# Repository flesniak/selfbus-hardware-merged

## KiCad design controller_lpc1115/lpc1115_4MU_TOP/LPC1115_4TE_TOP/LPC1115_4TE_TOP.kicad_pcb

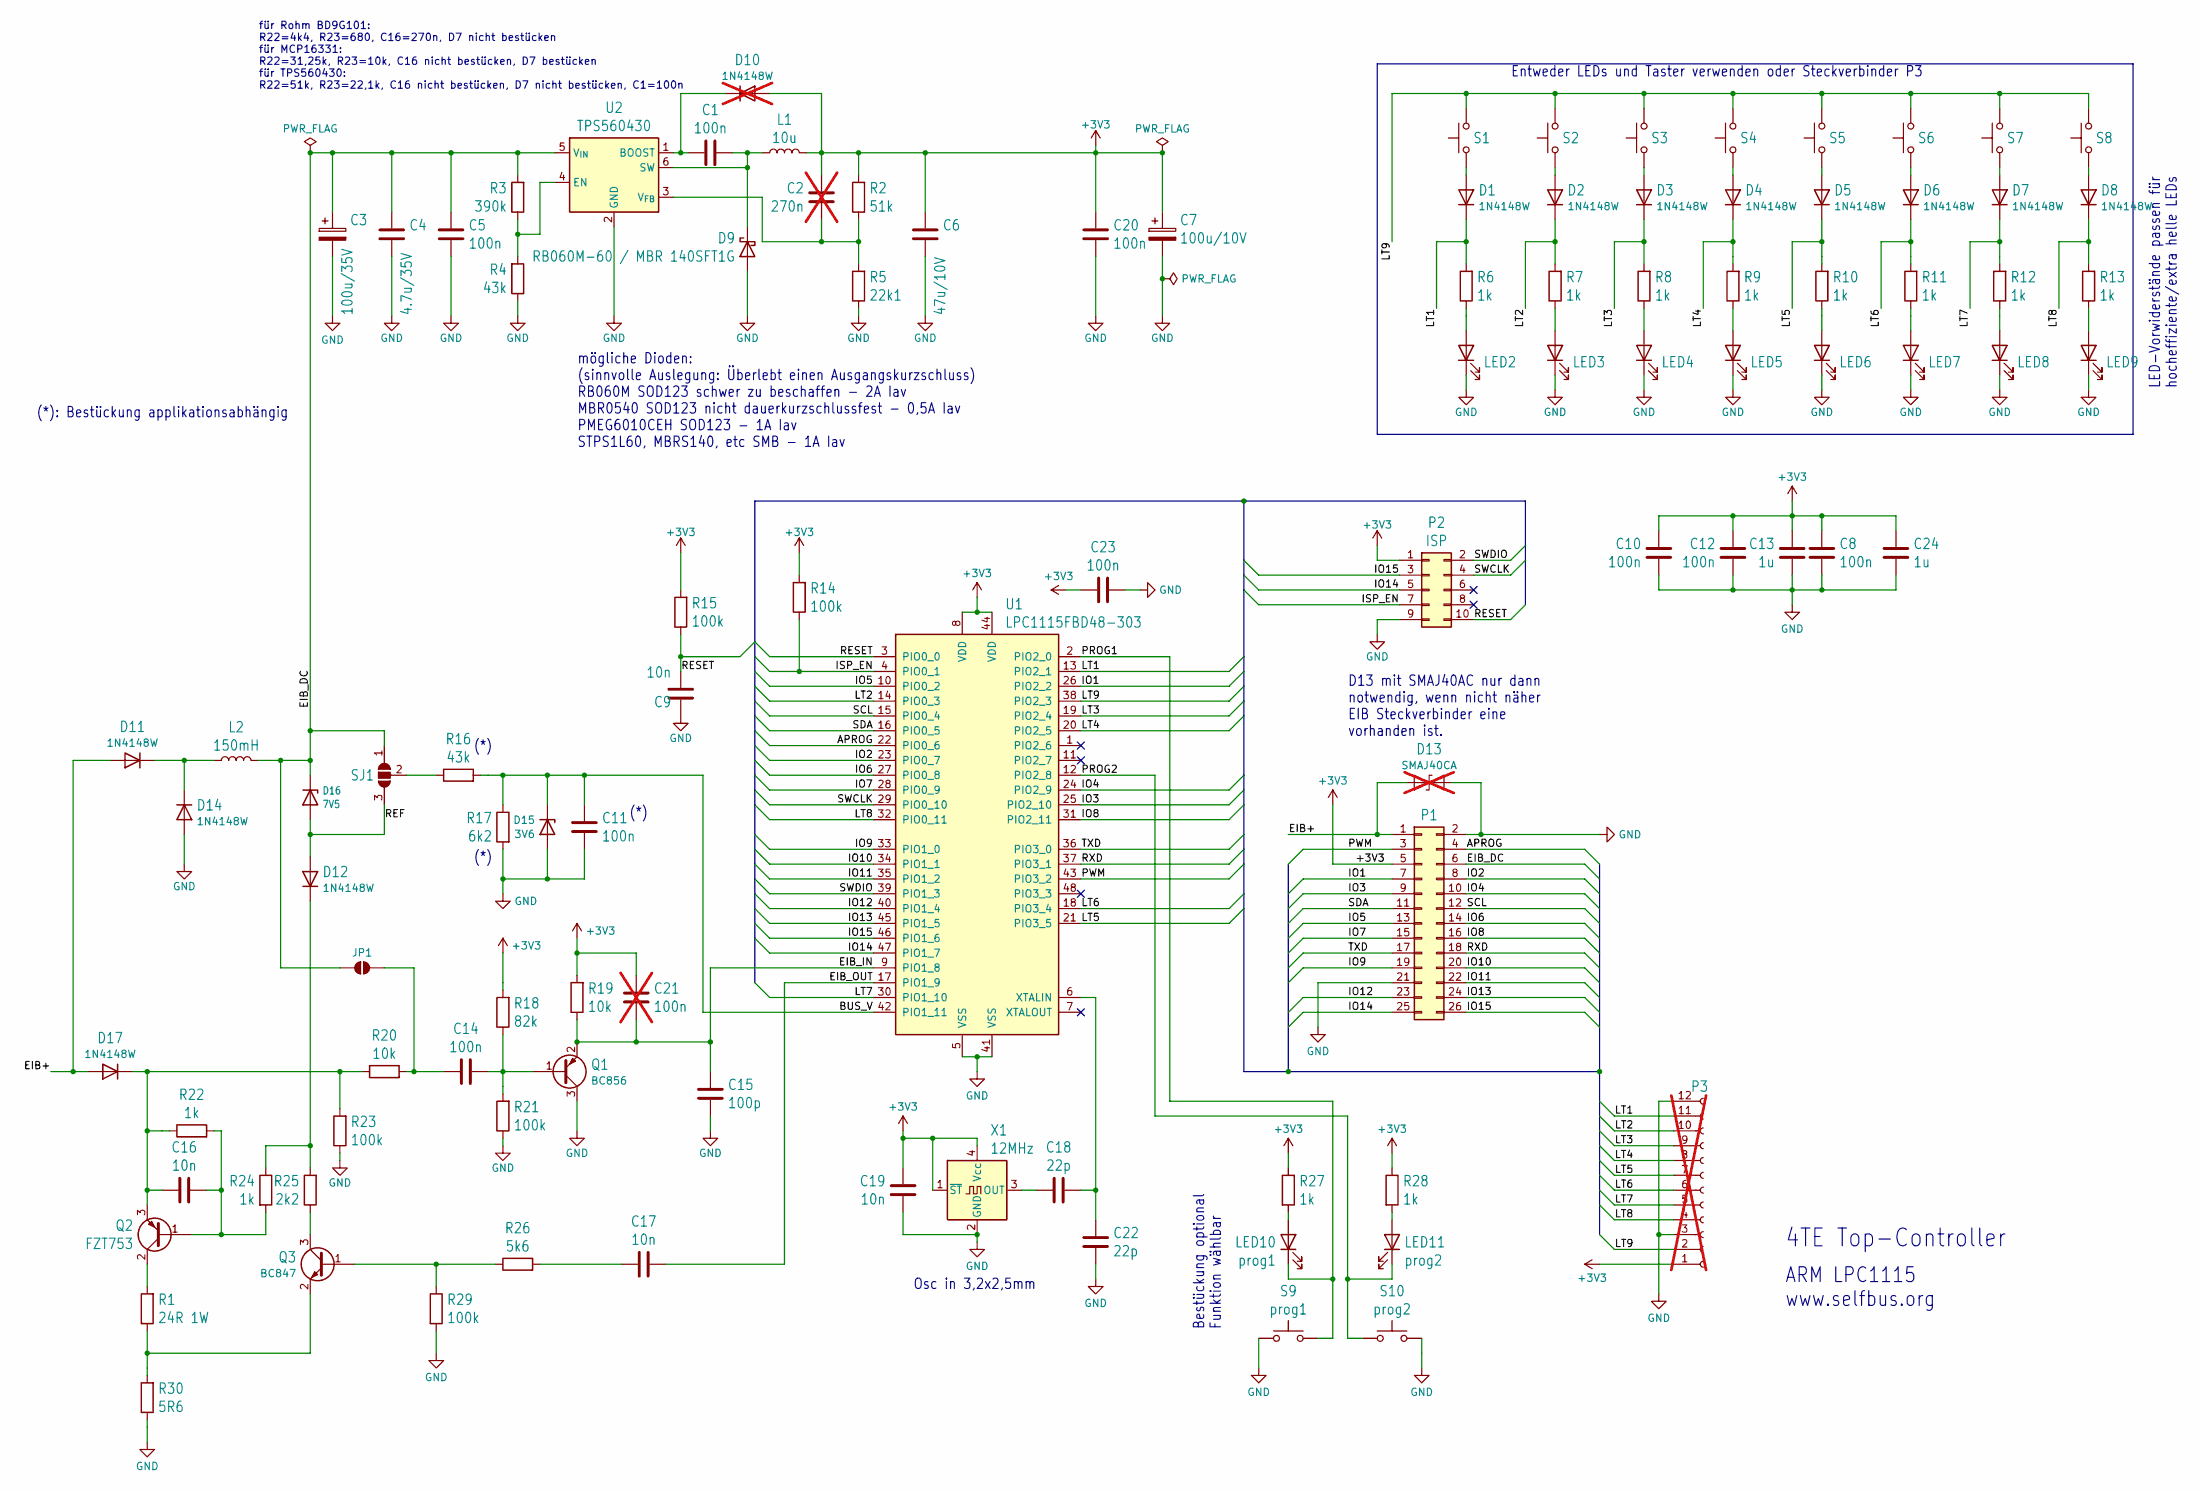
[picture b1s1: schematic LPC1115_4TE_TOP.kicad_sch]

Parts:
C1, C5, C8, C10, C11, C12, C14, C20, C23: 100n; C_0805_2012Metric
C2: 270n; C_0805_2012Metric; not fitted
C3: 100u/35V; CP_Elec_6.3x7.7
C4: 4.7u/35V; C_0805_2012Metric
C6: 47u/10V; C_1206_3216Metric
C7: 100u/10V; CP_Elec_6.3x7.7
C9, C16, C17, C19: 10n; C_0805_2012Metric
C13, C24: 1u; C_0805_2012Metric
C15: 100p; C_0805_2012Metric
C18, C22: 22p; C_0805_2012Metric
C21: 100n; C_0805_2012Metric; not fitted
D1, D2, D3, D4, D5, D6, D7, D8, D11, D12, D14, D17: 1N4148W; D_SOD-123
D9: RB060M-60 / MBR 140SFT1G; D_SOD-123
D10: 1N4148W; D_SOD-123; not fitted
D13: SMAJ40CA; D_SMA; not fitted
D15: 3V6; D_MiniMELF
D16: 7V5; D_MiniMELF
JP1: SolderJumper_2_Open; SolderJumper-2_P1.3mm_Open_Pad1.0x1.5mm
L1: 10u; L_1812_4532Metric
L2: 150mH; BS11_LIEGEND
LED2: CH1; LED_0805_2012Metric
LED3: CH2; LED_0805_2012Metric
LED4: CH3; LED_0805_2012Metric
LED5: CH4; LED_0805_2012Metric
LED6: CH5; LED_0805_2012Metric
LED7: CH6; LED_0805_2012Metric
LED8: CH7; LED_0805_2012Metric
LED9: CH8; LED_0805_2012Metric
LED10: prog1; LED_0805_2012Metric
LED11: prog2; LED_0805_2012Metric
P1: ML26; IDC-Header_2x13_P2.54mm_Vertical
P2: ISP; PinHeader_2x05_P2.00mm_Vertical
P3: FE12-1; PinHeader_1x12_P2.54mm_Vertical; not fitted
Q1: BC856; SOT-23
Q2: FZT753; SOT-223-3_TabPin2
Q3: BC847; SOT-23
R1: 24R 1W; R_2512_6332Metric
R2: 51k; R_0805_2012Metric
R3: 390k; R_0805_2012Metric
R4, R16: 43k; R_0805_2012Metric
R5: 22k1; R_0805_2012Metric
R6, R7, R8, R9, R10, R11, R12, R13, R22, R24, R27, R28: 1k; R_0805_2012Metric
R14, R15, R21, R23, R29: 100k; R_0805_2012Metric
R17: 6k2; R_0805_2012Metric
R18: 82k; R_0805_2012Metric
R19, R20: 10k; R_0805_2012Metric
R25: 2k2; R_0805_2012Metric
R26: 5k6; R_0805_2012Metric
R30: 5R6; R_0805_2012Metric
S1: CH1; SW_SPST_Omron_B3FS-100xP
S2: CH2; SW_SPST_Omron_B3FS-100xP
S3: CH3; SW_SPST_Omron_B3FS-100xP
S4: CH4; SW_SPST_Omron_B3FS-100xP
S5: CH5; SW_SPST_Omron_B3FS-100xP
S6: CH6; SW_SPST_Omron_B3FS-100xP
S7: CH7; SW_SPST_Omron_B3FS-100xP
S8: CH8; SW_SPST_Omron_B3FS-100xP
S9: prog1; SW_SPST_Omron_B3FS-100xP
S10: prog2; SW_SPST_Omron_B3FS-100xP
SJ1: SolderJumper_3_Open; SolderJumper-3_P1.3mm_Open_Pad1.0x1.5mm
U1: LPC1115FBD48-303; LQFP-48_7x7mm_P0.5mm
U2: TPS560430; SOT-23-6
X1: 12MHz; Oscillator_SMD_SeikoEpson_SG210-4Pin_2.5x2.0mm

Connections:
+3V3: C2.1, C6.1, C7.1, C8.1, C10.1, C12.1, C13.1, C19.1, C20.1, C21.2, C23.1, C24.1, D10.2 (A), L1.2, P1.5, P2.1, P3.1, R2.2, R14.2, R15.2, R18.2, R19.2, R27.1, R28.1, U1.8 (VDD), U1.44 (VDD), X1.1 (~ST), X1.4 (Vcc)
/APROG: P1.4, U1.22 (PIO0_6)
/BUS_V: C11.1, D15.1 (K), R16.2, R17.1, U1.42 (PIO1_11)
/EIB+: D11.2 (A), D13.2 (A2), D17.2 (A), P1.1
/EIB_DC: C3.1, C4.1, C5.1, D16.1 (K), JP1.1 (A), L2.2, P1.6, R3.2, SJ1.1 (A), U2.5 (V_{IN})
/EIB_IN: C15.2, C21.1, Q1.2 (E), R19.1, U1.9 (PIO1_8)
/EIB_OUT: C17.2, U1.17 (PIO1_9)
/IO1: P1.7, U1.26 (PIO2_2)
/IO2: P1.8, U1.23 (PIO0_7)
/IO3: P1.9, U1.25 (PIO2_10)
/IO4: P1.10, U1.24 (PIO2_9)
/IO5: P1.13, U1.10 (PIO0_2)
/IO6: P1.14, U1.27 (PIO0_8)
/IO7: P1.15, U1.28 (PIO0_9)
/IO8: P1.16, U1.31 (PIO2_11)
/IO9: P1.19, U1.33 (PIO1_0)
/IO10: P1.20, U1.34 (PIO1_1)
/IO11: P1.22, U1.35 (PIO1_2)
/IO12: P1.23, U1.40 (PIO1_4)
/IO13: P1.24, U1.45 (PIO1_5)
/IO14: P1.25, P2.5, U1.47 (PIO1_7)
/IO15: P1.26, P2.3, U1.46 (PIO1_6)
/ISP_EN: P2.7, R14.1, U1.4 (PIO0_1)
/LT1: D1.1 (K), P3.11, R6.2, U1.13 (PIO2_1)
/LT2: D2.1 (K), P3.10, R7.2, U1.14 (PIO0_3)
/LT3: D3.1 (K), P3.9, R8.2, U1.19 (PIO2_4)
/LT4: D4.1 (K), P3.8, R9.2, U1.20 (PIO2_5)
/LT5: D5.1 (K), P3.7, R10.2, U1.21 (PIO3_5)
/LT6: D6.1 (K), P3.6, R11.2, U1.18 (PIO3_4)
/LT7: D7.1 (K), P3.5, R12.2, U1.30 (PIO1_10)
/LT8: D8.1 (K), P3.4, R13.2, U1.32 (PIO0_11)
/LT9: P3.2, S1.1, S2.1, S3.1, S4.1, S5.1, S6.1, S7.1, S8.1, U1.38 (PIO2_3)
/PROG1: LED10.1 (K), S9.1, U1.2 (PIO2_0)
/PROG2: LED11.1 (K), S10.1, U1.12 (PIO2_8)
/PWM: P1.3, U1.43 (PIO3_2)
/REF: D12.2 (A), D16.2 (A), SJ1.3 (B)
/RESET: C9.2, P2.10, R15.1, U1.3 (PIO0_0)
/RXD: P1.18, U1.37 (PIO3_1)
/SCL: P1.12, U1.15 (PIO0_4)
/SDA: P1.11, U1.16 (PIO0_5)
/SWCLK: P2.4, U1.29 (PIO0_10)
/SWDIO: P2.2, U1.39 (PIO1_3)
/TXD: P1.17, U1.36 (PIO3_0)
GND: C3.2, C4.2, C5.2, C6.2, C7.2, C8.2, C9.1, C10.2, C11.2, C12.2, C13.2, C15.1, C19.2, C20.2, C22.2, C23.2, C24.2, D9.2 (A), D13.1 (A1), D14.2 (A), D15.2 (A), LED2.1 (K), LED3.1 (K), LED4.1 (K), LED5.1 (K), LED6.1 (K), LED7.1 (K), LED8.1 (K), LED9.1 (K), P1.2, P1.21, P2.9, P3.3, P3.12, Q1.3 (C), R4.1, R5.1, R17.2, R21.1, R23.1, R29.2, R30.1, S9.2, S10.2, U1.5 (VSS), U1.41 (VSS), U2.2 (GND), X1.2 (GND)
unnamed: C17.1, R26.2
unnamed: D1.2 (A), S1.2
unnamed: D2.2 (A), S2.2
unnamed: D3.2 (A), S3.2
unnamed: D4.2 (A), S4.2
unnamed: D5.2 (A), S5.2
unnamed: D6.2 (A), S6.2
unnamed: D7.2 (A), S7.2
unnamed: D8.2 (A), S8.2
unnamed: C1.1, D9.1 (K), L1.1, U2.6 (SW)
unnamed: C1.2, D10.1 (K), U2.1 (BOOST)
unnamed: D11.1 (K), D14.1 (K), L2.1
unnamed: D12.1 (K), R24.1, R25.2
unnamed: C16.1, D17.1 (K), Q2.3 (E), R20.1, R22.1, R23.2
unnamed: C14.1, JP1.2 (B), R20.2
unnamed: LED2.2 (A), R6.1
unnamed: LED3.2 (A), R7.1
unnamed: LED4.2 (A), R8.1
unnamed: LED5.2 (A), R9.1
unnamed: LED6.2 (A), R10.1
unnamed: LED7.2 (A), R11.1
unnamed: LED8.2 (A), R12.1
unnamed: LED9.2 (A), R13.1
unnamed: LED10.2 (A), R27.2
unnamed: LED11.2 (A), R28.2
unnamed: C14.2, Q1.1 (B), R18.1, R21.2
unnamed: C16.2, Q2.1 (B), R22.2, R24.2
unnamed: Q2.2 (C), R1.2
unnamed: Q3.1 (B), R26.1, R29.1
unnamed: Q3.3 (C), R25.1
unnamed: Q3.2 (E), R1.1, R30.2
unnamed: R16.1, SJ1.2 (C)
unnamed: C18.2, C22.1, U1.6 (XTALIN)
unnamed: R3.1, R4.2, U2.4 (EN)
unnamed: C2.2, R2.1, R5.2, U2.3 (V_{FB})
unnamed: C18.1, X1.3 (OUT)

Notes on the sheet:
4TE Top-Controller
(*): Bestückung applikationsabhängig
(*)
LED-Vorwiderstände passen für hocheffiziente/extra helle LEDs
mögliche Dioden: (sinnvolle Auslegung: Überlebt einen Ausgangskurzschluss) RB060M SOD123 schwer zu beschaffen - 2A Iav MBR0540 SOD123 nicht dauerkurzschlussfest - 0,5A Iav PMEG6010CEH SOD123 - 1A Iav STPS1L60, MBRS140, etc SMB - 1A Iav
Entweder LEDs und Taster verwenden oder Steckverbinder P3
ARM LPC1115 www.selfbus.org
für Rohm BD9G101: R22=4k4, R23=680, C16=270n, D7 nicht bestücken für MCP16331: R22=31,25k, R23=10k, C16 nicht bestücken, D7 bestücken für TPS560430: R22=51k, R23=22,1k, C16 nicht bestücken, D7 nicht bestücken, C1=100n
Bestückung optional Funktion wählbar
D13 mit SMAJ40AC nur dann notwendig, wenn nicht näher EIB Steckverbinder eine vorhanden ist.
Osc in 3,2x2,5mm

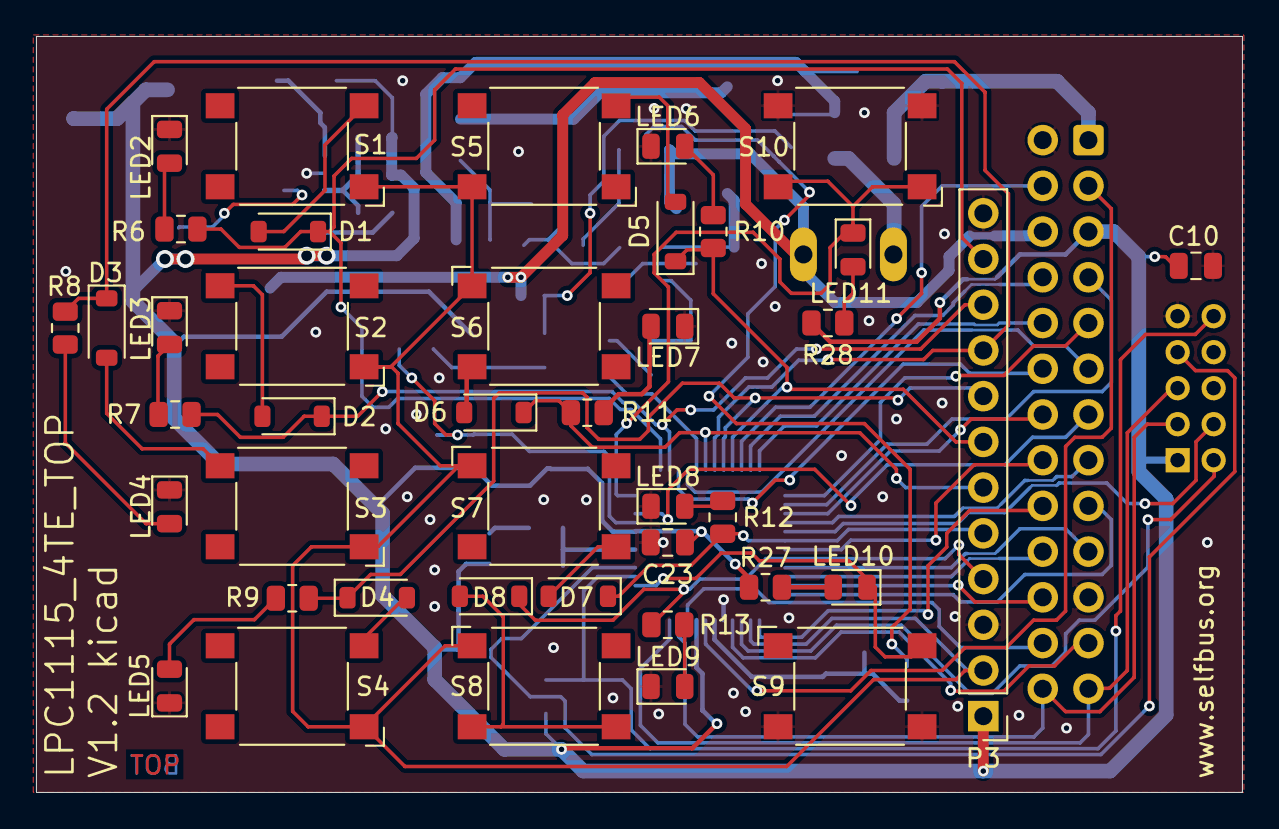
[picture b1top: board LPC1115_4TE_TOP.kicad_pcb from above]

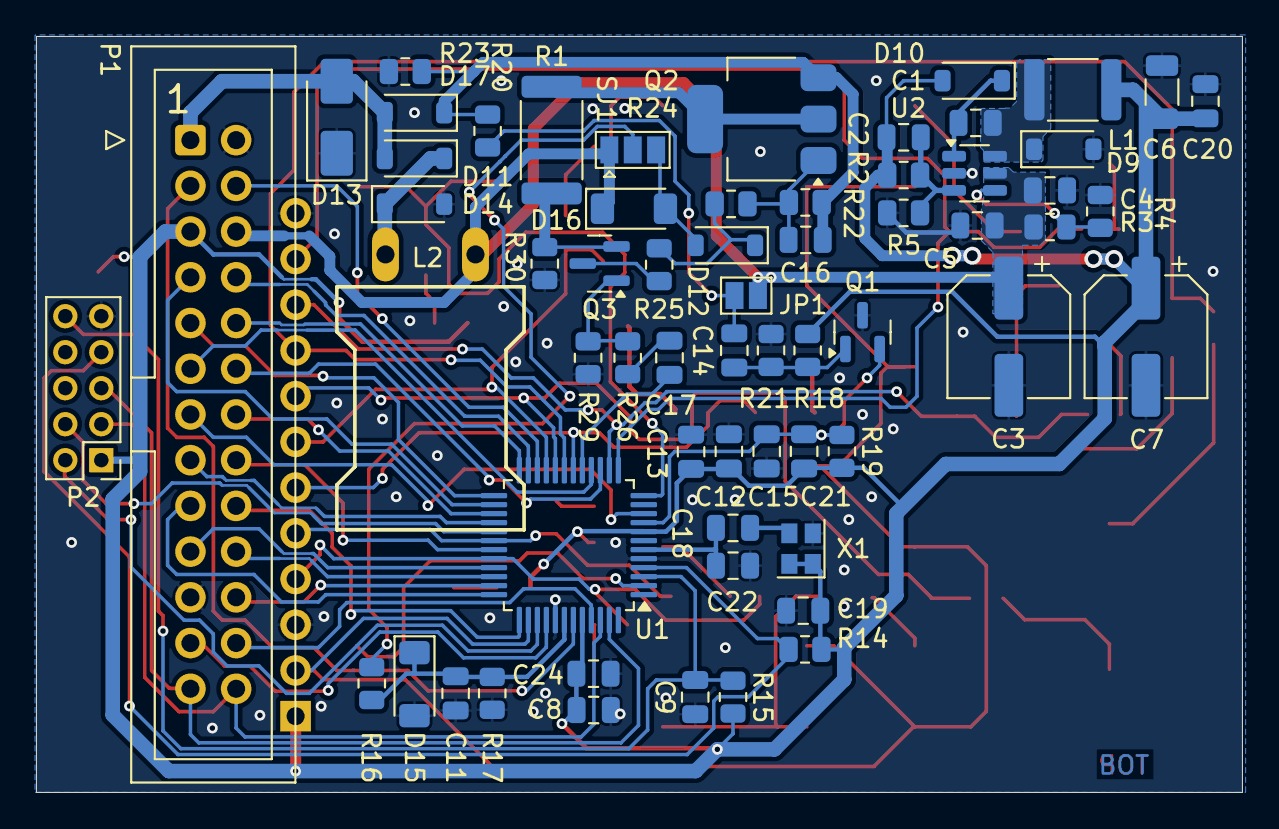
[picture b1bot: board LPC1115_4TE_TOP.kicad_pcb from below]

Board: 2 copper layers, 67.0 x 42.0 mm, 104 parts (63 on the bottom side), 80 nets.

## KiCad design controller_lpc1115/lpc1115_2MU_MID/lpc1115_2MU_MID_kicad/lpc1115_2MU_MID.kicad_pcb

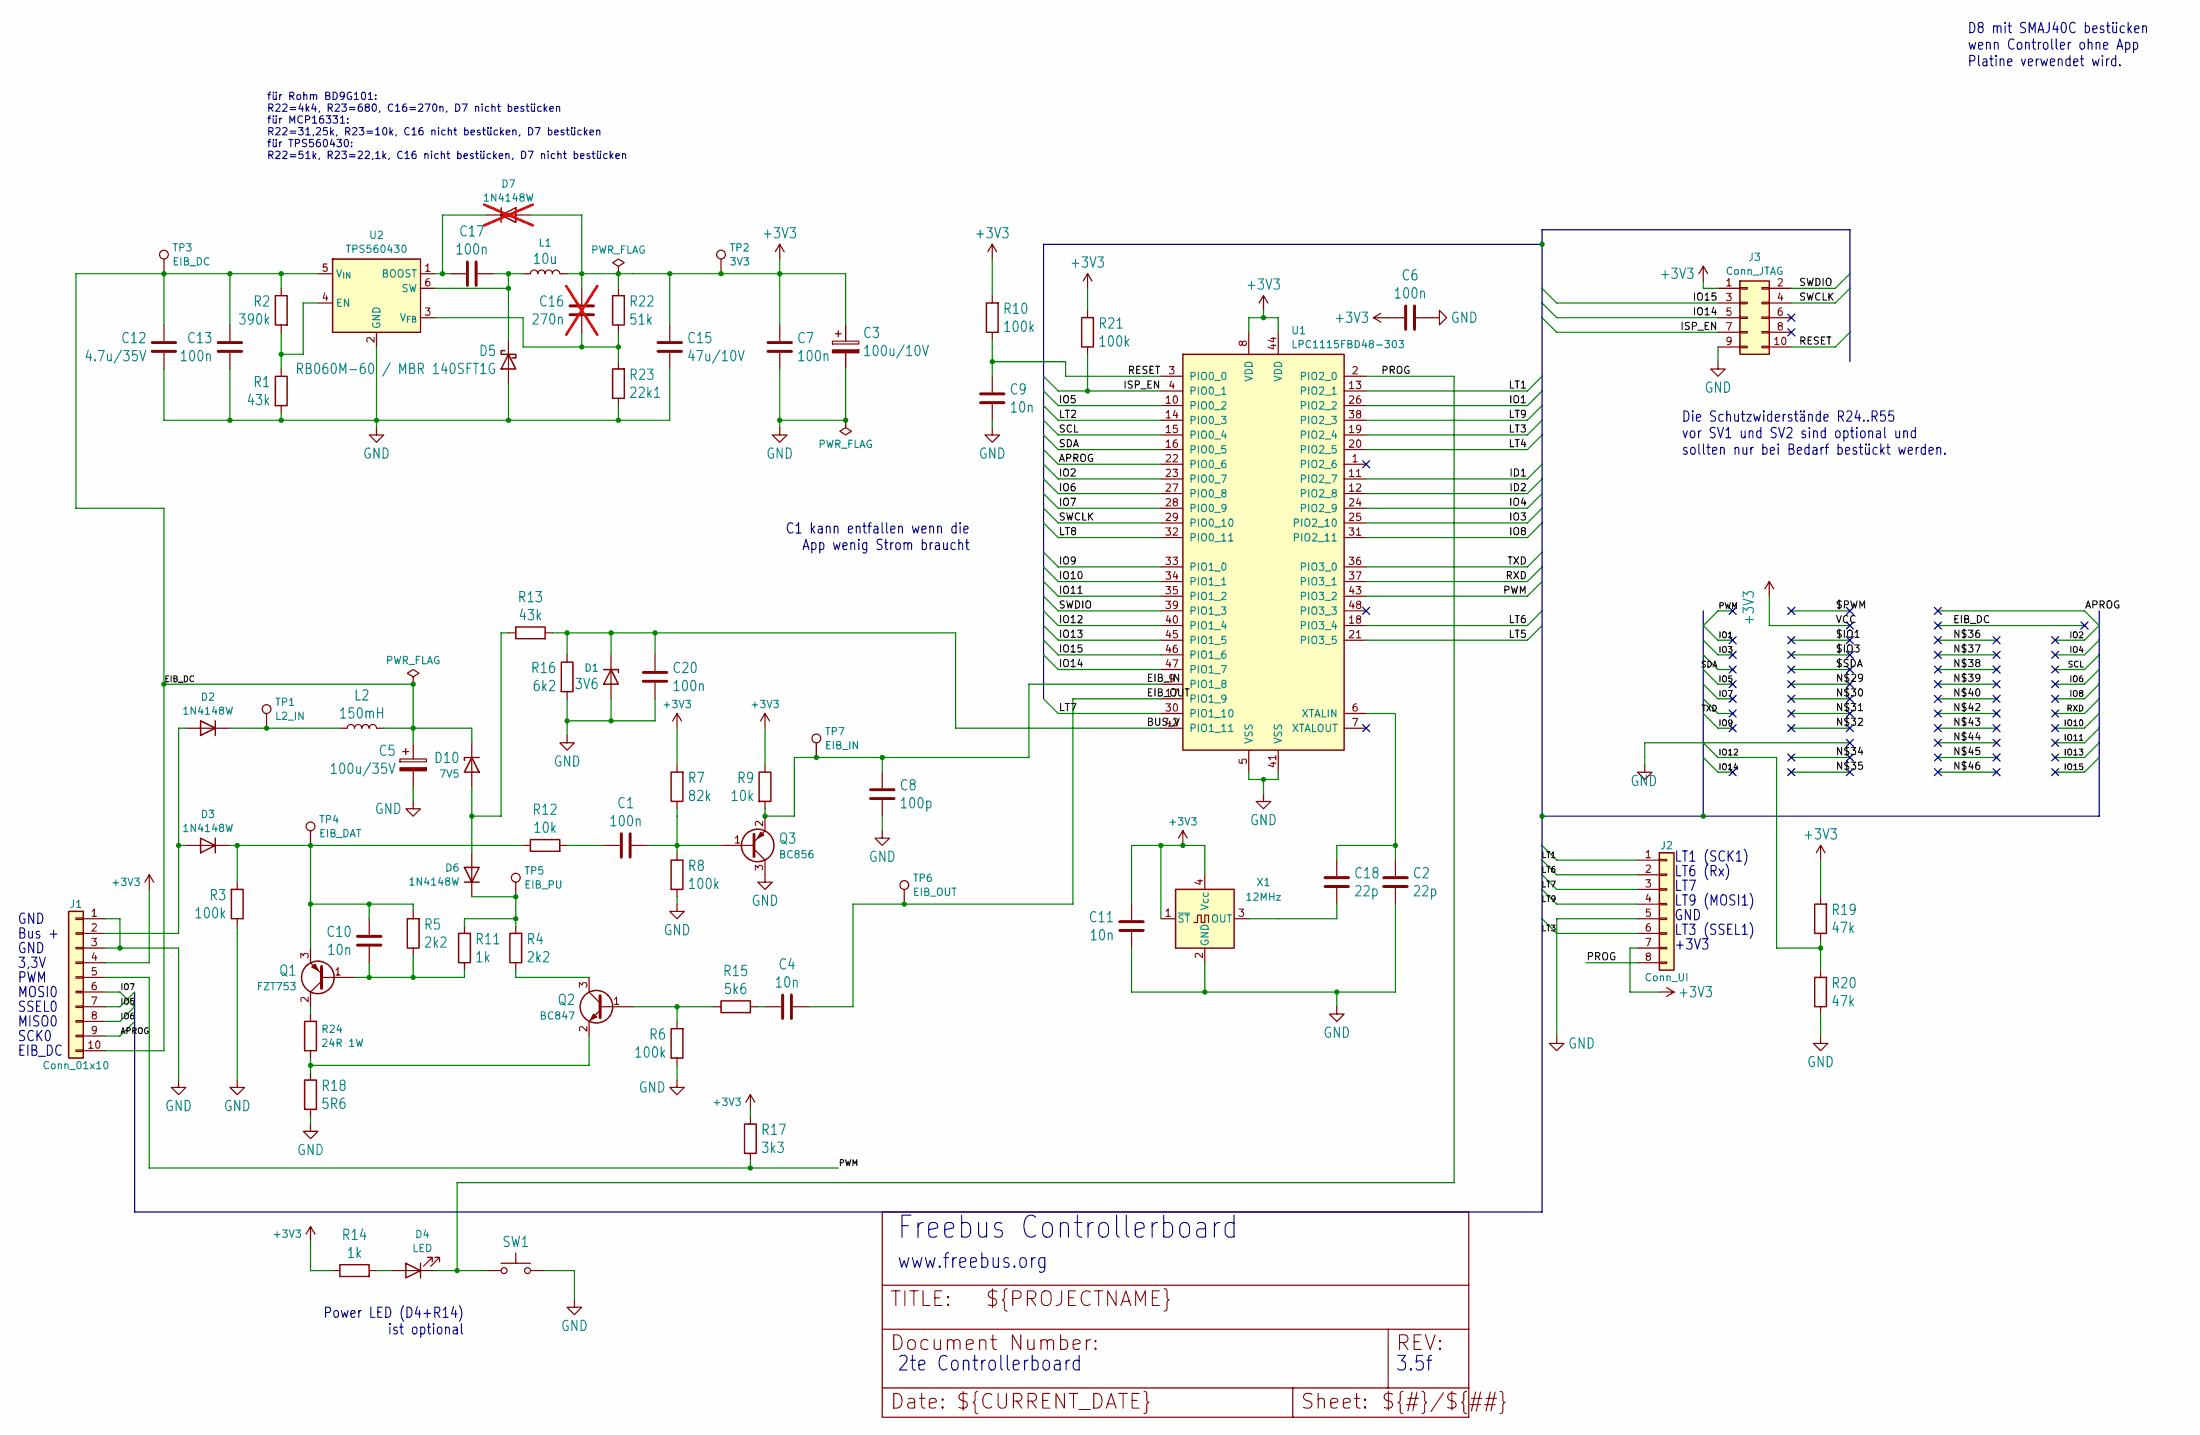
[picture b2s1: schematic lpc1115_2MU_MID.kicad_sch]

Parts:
C1, C6, C7, C13, C17, C20: 100n; C_0805_2012Metric
C2, C18: 22p; C_0805_2012Metric
C3: 100u/10V; CP_Elec_6.3x7.7
C4, C9, C10, C11: 10n; C_0805_2012Metric
C5: 100u/35V; CP_Elec_6.3x7.7
C8: 100p; C_0805_2012Metric
C12: 4.7u/35V; C_0805_2012Metric
C15: 47u/10V; C_1206_3216Metric
C16: 270n; C_0805_2012Metric; not fitted
D1: 3V6; D_MiniMELF
D2, D3, D6: 1N4148W; D_SOD-123
D4: LED; LED_0805_2012Metric
D5: RB060M-60 / MBR 140SFT1G; D_SOD-123
D7: 1N4148W; D_SOD-123; not fitted
D10: 7V5; D_MiniMELF
J1: Conn_01x10; Molex_KK-254_AE-6410-10A_1x10_P2.54mm_Vertical
J2: Conn_UI; PinHeader_1x08_P2.54mm_Vertical
J3: Conn_JTAG; PinHeader_2x05_P2.00mm_Vertical
L1: 10u; L_1812_4532Metric
L2: 150mH; BS11_LIEGEND
Q1: FZT753; SOT-223-3_TabPin2
Q2: BC847; SOT-23
Q3: BC856; SOT-23
R1, R13: 43k; R_0805_2012Metric
R2: 390k; R_0805_2012Metric
R3, R6, R8, R10, R21: 100k; R_0805_2012Metric
R4, R5: 2k2; R_0805_2012Metric
R7: 82k; R_0805_2012Metric
R9, R12: 10k; R_0805_2012Metric
R11, R14: 1k; R_0805_2012Metric
R15: 5k6; R_0805_2012Metric
R16: 6k2; R_0805_2012Metric
R17: 3k3; R_0805_2012Metric
R18: 5R6; R_0805_2012Metric
R19, R20: 47k; R_0805_2012Metric
R22: 51k; R_0805_2012Metric
R23: 22k1; R_0805_2012Metric
R24: 24R 1W; R_2512_6332Metric
SW1: SW_Omron_B3FS; SW_SPST_Omron_B3FS-100xP
TP1: L2_IN; TestPoint_Pad_D1.0mm
TP2: 3V3; TestPoint_Pad_D1.0mm
TP3: EIB_DC; TestPoint_Pad_D1.0mm
TP4: EIB_DAT; TestPoint_Pad_D1.0mm
TP5: EIB_PU; TestPoint_Pad_D1.0mm
TP6: EIB_OUT; TestPoint_Pad_D1.0mm
TP7: EIB_IN; TestPoint_Pad_D1.0mm
U1: LPC1115FBD48-303; LQFP-48_7x7mm_P0.5mm
U2: TPS560430; SOT-23-6
X1: 12MHz; Oscillator_SMD_SeikoEpson_SG210-4Pin_2.5x2.0mm

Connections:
+3V3: C3.1, C6.2, C7.2, C11.2, C15.2, C16.2, D7.2 (A), J1.4, J2.7, J3.1, L1.2, R7.2, R9.1, R10.2, R14.1, R17.1, R19.2, R21.2, R22.2, TP2.1, U1.8 (VDD), U1.44 (VDD), X1.1 (~ST), X1.4 (Vcc)
/APROG: J1.9, U1.22 (PIO0_6)
/BUS_V: C20.2, D1.1 (K), R13.2, R16.1, U1.42 (PIO1_11)
/EIB_DC: C5.1, C12.2, C13.2, D10.1 (K), J1.10, L2.2, R2.1, TP3.1, U2.5 (V_{IN})
/EIB_IN: C8.2, Q3.2 (E), R9.2, TP7.1, U1.9 (PIO1_8)
/EIB_OUT: C4.1, TP6.1, U1.17 (PIO1_9)
/ID1: U1.11 (PIO2_7)
/ID2: U1.12 (PIO2_8)
/IO1: U1.26 (PIO2_2)
/IO2: U1.23 (PIO0_7)
/IO3: U1.25 (PIO2_10)
/IO4: U1.24 (PIO2_9)
/IO5: J1.7, U1.10 (PIO0_2)
/IO6: J1.8, U1.27 (PIO0_8)
/IO7: J1.6, U1.28 (PIO0_9)
/IO8: U1.31 (PIO2_11)
/IO9: U1.33 (PIO1_0)
/IO10: U1.34 (PIO1_1)
/IO11: U1.35 (PIO1_2)
/IO12: R19.1, R20.2, U1.40 (PIO1_4)
/IO13: U1.45 (PIO1_5)
/IO14: J3.5, U1.47 (PIO1_7)
/IO15: J3.3, U1.46 (PIO1_6)
/ISP_EN: J3.7, R21.1, U1.4 (PIO0_1)
/LT1: J2.1, U1.13 (PIO2_1)
/LT2: U1.14 (PIO0_3)
/LT4: U1.20 (PIO2_5)
/LT5: U1.21 (PIO3_5)
/LT6: J2.2, U1.18 (PIO3_4)
/LT7: J2.3, U1.30 (PIO1_10)
/LT8: U1.32 (PIO0_11)
/LT9: J2.4, U1.38 (PIO2_3)
/PROG: D4.1 (K), J2.8, SW1.1, U1.2 (PIO2_0)
/PWM: J1.5, R17.2, U1.43 (PIO3_2)
/RESET: C9.2, J3.10, R10.1, U1.3 (PIO0_0)
/RXD: U1.37 (PIO3_1)
/SCL: U1.15 (PIO0_4)
/SDA: U1.16 (PIO0_5)
/SWCLK: J3.4, U1.29 (PIO0_10)
/SWDIO: J3.2, U1.39 (PIO1_3)
/TXD: U1.36 (PIO3_0)
GND: C2.1, C3.2, C5.2, C6.1, C7.1, C8.1, C9.1, C11.1, C12.1, C13.1, C15.1, C20.1, D1.2 (A), D5.2 (A), J1.1, J1.3, J2.5, J2.6, J3.9, Q3.3 (C), R1.2, R3.1, R6.1, R8.2, R16.2, R18.2, R20.1, R23.1, SW1.2, U1.5 (VSS), U1.19 (PIO2_4), U1.41 (VSS), U2.2 (GND), X1.2 (GND)
unnamed: C1.1, R12.2
unnamed: C4.2, R15.2
unnamed: D2.2 (A), D3.2 (A), J1.2
unnamed: D2.1 (K), L2.1, TP1.1
unnamed: C10.2, D3.1 (K), Q1.3 (E), R3.2, R5.2, R12.1, TP4.1
unnamed: D4.2 (A), R14.2
unnamed: C17.2, D5.1 (K), L1.1, U2.6 (SW)
unnamed: D6.1 (K), R4.2, R11.2, TP5.1
unnamed: C17.1, D7.1 (K), U2.1 (BOOST)
unnamed: D6.2 (A), D10.2 (A), R13.1
unnamed: C10.1, Q1.1 (B), R5.1, R11.1
unnamed: Q1.2 (C), R24.1
unnamed: Q2.1 (B), R6.2, R15.1
unnamed: Q2.3 (C), R4.1
unnamed: Q2.2 (E), R18.1, R24.2
unnamed: C1.2, Q3.1 (B), R7.1, R8.1
unnamed: C2.2, C18.2, U1.6 (XTALIN)
unnamed: R1.1, R2.2, U2.4 (EN)
unnamed: C16.1, R22.1, R23.2, U2.3 (V_{FB})
unnamed: C18.1, X1.3 (OUT)

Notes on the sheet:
www.freebus.org
3.5f
für Rohm BD9G101: R22=4k4, R23=680, C16=270n, D7 nicht bestücken für MCP16331: R22=31,25k, R23=10k, C16 nicht bestücken, D7 bestücken für TPS560430: R22=51k, R23=22,1k, C16 nicht bestücken, D7 nicht bestücken
C1 kann entfallen wenn die App wenig Strom braucht
LT7
Die Schutzwiderstände R24..R55 vor SV1 und SV2 sind optional und sollten nur bei Bedarf bestückt werden.
GND
SCK0
2te Controllerboard
LT6 (Rx)
SSEL0
LT1 (SCK1)
Freebus Controllerboard
Power LED (D4+R14) ist optional
3,3V
+3V3
MOSI0
LT3 (SSEL1)
PWM
D8 mit SMAJ40C bestücken wenn Controller ohne App Platine verwendet wird.
LT9 (MOSI1)
Bus +
MISO0
EIB_DC

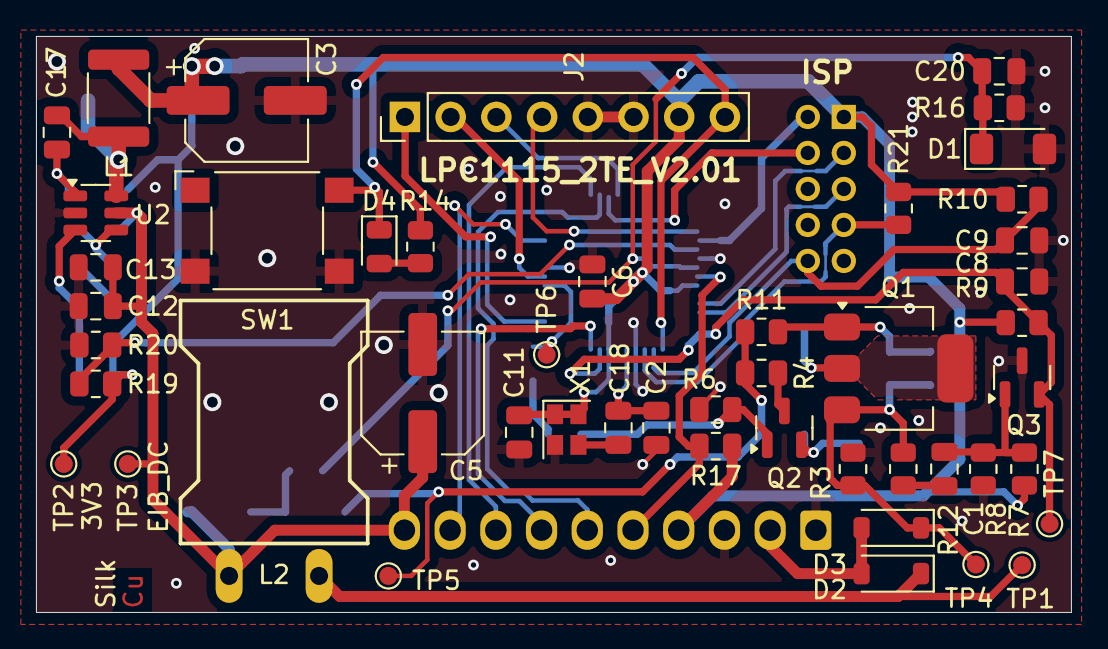
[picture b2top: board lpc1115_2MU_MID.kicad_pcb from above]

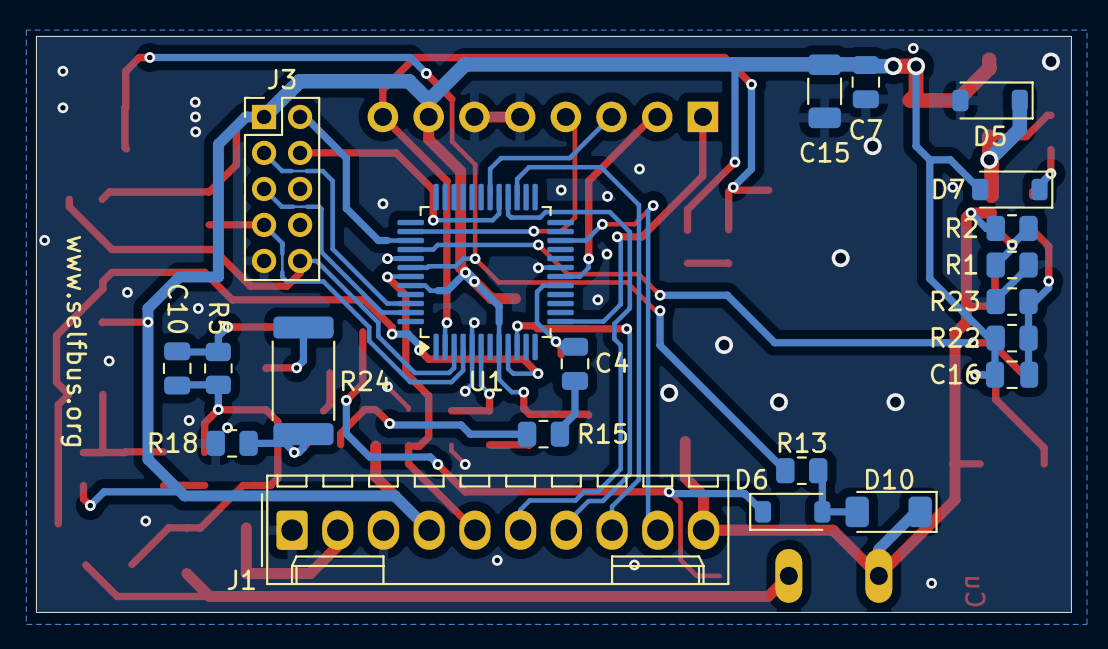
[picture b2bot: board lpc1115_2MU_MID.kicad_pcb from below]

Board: 2 copper layers, 57.5 x 32.0 mm, 69 parts (21 on the bottom side), 43 nets.

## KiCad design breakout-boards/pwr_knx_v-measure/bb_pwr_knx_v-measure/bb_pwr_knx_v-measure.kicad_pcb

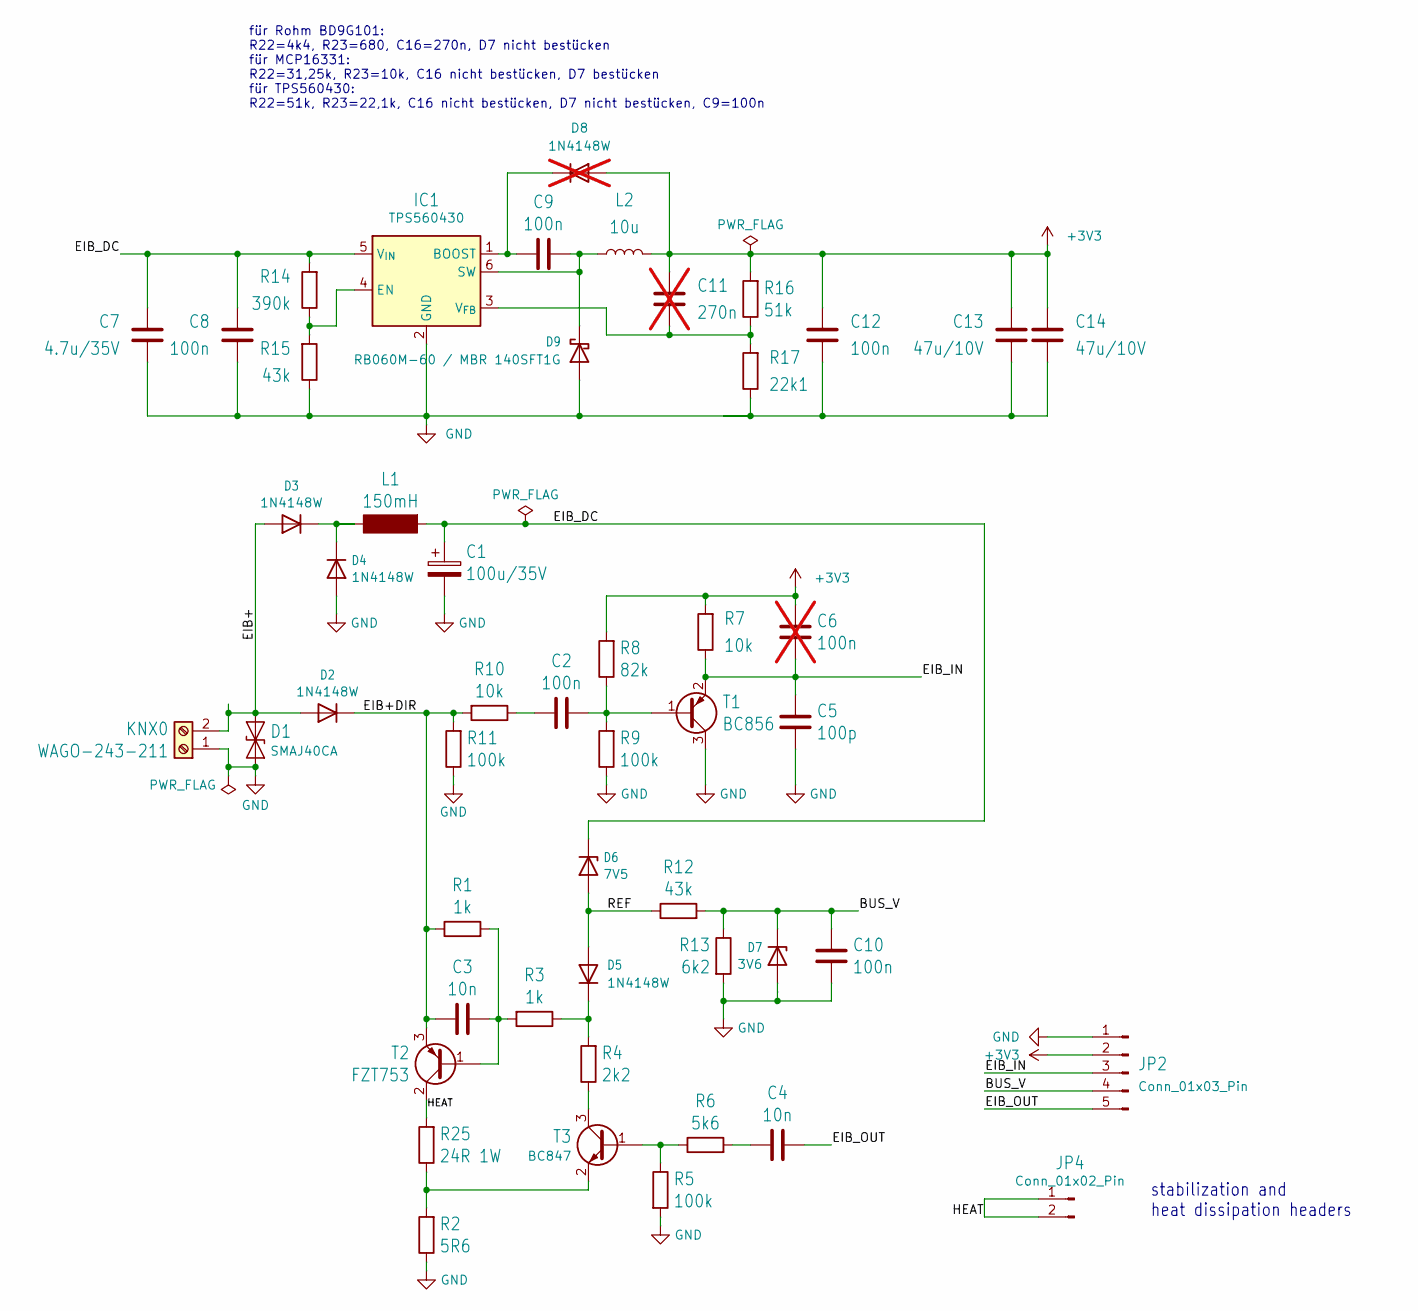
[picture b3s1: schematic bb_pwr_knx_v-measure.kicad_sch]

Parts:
C1: 100u/35V; CP_Elec_6.3x7.7
C2, C8, C9, C10, C12: 100n; C_0805_2012Metric
C3, C4: 10n; C_0805_2012Metric
C5: 100p; C_0805_2012Metric
C6: 100n; C_0805_2012Metric; not fitted
C7: 4.7u/35V; C_0805_2012Metric
C11: 270n; C_0805_2012Metric; not fitted
C13, C14: 47u/10V; C_1206_3216Metric
D1: SMAJ40CA; D_SMA
D2, D3, D4, D5: 1N4148W; D_SOD-123
D6: 7V5; D_MiniMELF
D7: 3V6; D_MiniMELF
D8: 1N4148W; D_SOD-123; not fitted
D9: RB060M-60 / MBR 140SFT1G; D_SOD-123
IC1: TPS560430; SOT-23-6
JP2: Conn_01x03_Pin; PinHeader_1x05_P2.54mm_Vertical
JP4: Conn_01x02_Pin; PinHeader_1x02_P2.54mm_Vertical
KNX0: WAGO-243-211; W243-211_1x02_P5.75
L1: 150mH; BS11_LIEGEND
L2: 10u; L_1812_4532Metric
R1, R3: 1k; R_0805_2012Metric
R2: 5R6; R_0805_2012Metric
R4: 2k2; R_0805_2012Metric
R5, R9, R11: 100k; R_0805_2012Metric
R6: 5k6; R_0805_2012Metric
R7, R10: 10k; R_0805_2012Metric
R8: 82k; R_0805_2012Metric
R12, R15: 43k; R_0805_2012Metric
R13: 6k2; R_0805_2012Metric
R14: 390k; R_0805_2012Metric
R16: 51k; R_0805_2012Metric
R17: 22k1; R_0805_2012Metric
R25: 24R 1W; R_2512_6332Metric
T1: BC856; SOT-23
T2: FZT753; SOT-223-3_TabPin2
T3: BC847; SOT-23

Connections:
+3V3: C6.2, C11.2, C12.1, C13.1, C14.1, D8.2 (A), JP2.2, L2.2, R7.2, R8.2, R16.2
/BUS_V: C10.2, D7.1 (K), JP2.4, R12.2, R13.1
/EIB+: D1.2 (A2), D2.2 (A), D3.2 (A), KNX0.2
/EIB+DIR: C3.1, D2.1 (K), R1.1, R10.2, R11.2, T2.3 (E)
/EIB_DC: C1.1, C7.2, C8.1, D6.1 (K), IC1.5 (V_{IN}), L1.1, R14.2
/EIB_IN: C5.2, C6.1, JP2.3, R7.1, T1.2 (E)
/EIB_OUT: C4.2, JP2.5
/HEAT: JP4.1, JP4.2, R25.2, T2.2 (C)
/REF: D5.2 (A), D6.2 (A), R12.1
GND: C1.2, C5.1, C7.1, C8.2, C10.1, C12.2, C13.2, C14.2, D1.1 (A1), D4.2 (A), D7.2 (A), D9.2 (A), IC1.2 (GND), JP2.1, KNX0.1, R2.1, R5.2, R9.1, R11.1, R13.2, R15.1, R17.1, T1.3 (C)
unnamed: C2.2, R10.1
unnamed: C4.1, R6.2
unnamed: D3.1 (K), D4.1 (K), L1.2
unnamed: D5.1 (K), R3.1, R4.2
unnamed: C9.2, D8.1 (K), IC1.1 (BOOST)
unnamed: C9.1, D9.1 (K), IC1.6 (SW), L2.1
unnamed: IC1.4 (EN), R14.1, R15.2
unnamed: C11.1, IC1.3 (V_{FB}), R16.1, R17.2
unnamed: C2.1, R8.1, R9.2, T1.1 (B)
unnamed: C3.2, R1.2, R3.2, T2.1 (B)
unnamed: R5.1, R6.1, T3.1 (B)
unnamed: R4.1, T3.3 (C)
unnamed: R2.2, R25.1, T3.2 (E)

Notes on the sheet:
stabilization and heat dissipation headers
für Rohm BD9G101: R22=4k4, R23=680, C16=270n, D7 nicht bestücken für MCP16331: R22=31,25k, R23=10k, C16 nicht bestücken, D7 bestücken für TPS560430: R22=51k, R23=22,1k, C16 nicht bestücken, D7 nicht bestücken, C9=100n

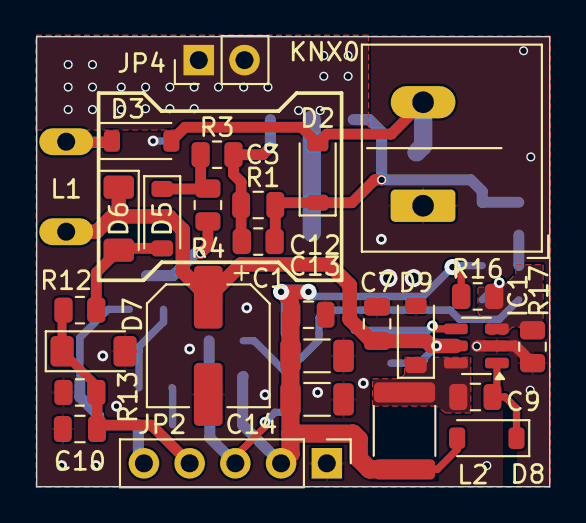
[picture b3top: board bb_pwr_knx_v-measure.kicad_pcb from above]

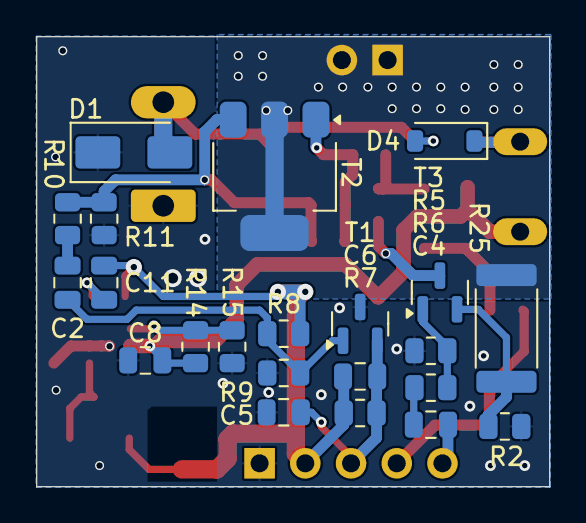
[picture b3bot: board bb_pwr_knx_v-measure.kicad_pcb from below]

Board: 2 copper layers, 28.5 x 25.0 mm, 50 parts (22 on the bottom side), 23 nets.
